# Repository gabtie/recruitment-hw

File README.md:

# Recruitment for E-Agle TRT | Electronics division

Welcome to the recruitment _test_ for the electronics team of E-Agle Trento Racing Team.

This _test_ is meant to give us the possibility to have a first understanding of the capabilities of our applicants without them having the pressure of seeing it as an exam.

Moreover it's studied so that the applicants get a first taste of the tools used, so that once in the team, they can get up and running quickly into the team's workflow without having to learn stuff under pressure when it's needed.

## What we'll look into

 - Understanding of basic electronics
 - Components choice and their suitability
 - KiCad
   - Schematic choices, tidyness and good practices
   - Board layout understanding and, again, good practices
 - `git` usage: fork, branch, clone, commit, push, pull
 - Not only _tecnical correctness_ but also actual usability.

## Assignment

Develop an overtemperature and overcurrent monitoring system (**monitor**) to perform plauysibility checks of a secondary system (**load**).

### Overview
The **monitor** has the following specs:
- It is supplied by an unstable DC voltage line, ranging from 9V to 17V
- Has a normally open relay connected in series with the load
- Has a hall effect sensor that measures the current through the load

The **load** has the following specs:
- Voltage range: $24[V] \div 48[V]$
- Current range: $-3[A] \div 25[A]$

### Specs
The **monitor** must ensure that the relay is open if the power obsorbed by the **load** is above $500[W]$.
Once open, it must not be possible to close the relay unless the **monitor** is power cycled.

No programmable logic is allowed.

The Hall effect based sensor can be chosen from the _Allegro ACS781xLR_ family of devices. Other sensors may be used as long as the specs are met and equivalency is proven.

Below you can find a general diagram of the system

## KiCad instructions
- In the schematic use also a hierarchical sheet
  - _It's not a good practice for such a small project, but it's for letting you learn about hierarchy without the hassle of a more complex assignment_

- Add comments for the necessary calculations of values

- Consider JLC PCB as the board manufacturer

## General instructions

 - Create a repository on your GitHub account (if you don't have it, create one) and copy this project in it. **Do not clone this repository!**
 - Branch the master into one called `name_surname` and commit your progress in this branch
 - Commit your progress along the way. **Do not commit just the finished project**, use Git for what it's made for!
 - When you are done, generate the schematic output inside `docs/` and the production (gerber) files in `output/`
 - If you haven't already, submit your application form [here](https://eagletrt.it/apply)
 - If you have any questions feel free to contact us at [electronics@eagletrt.it](mailto:electronics@eagletrt.it)
 - Feel free to also come to our lab (Povo 2 floor -2) if we are slow at replying
 - You have **2 weeks** (14 days) to work on this project (**This is a hard deadline and we evaluate if you meet deadlines**)

## Links
:globe_with_meridians: [Website](https://www.eagletrt.it)

:iphone: [Instagram](https://www.instagram.com/eagletrt)

:computer: [LinkedIn](https://www.linkedin.com/company/eagletrentoracingteam)

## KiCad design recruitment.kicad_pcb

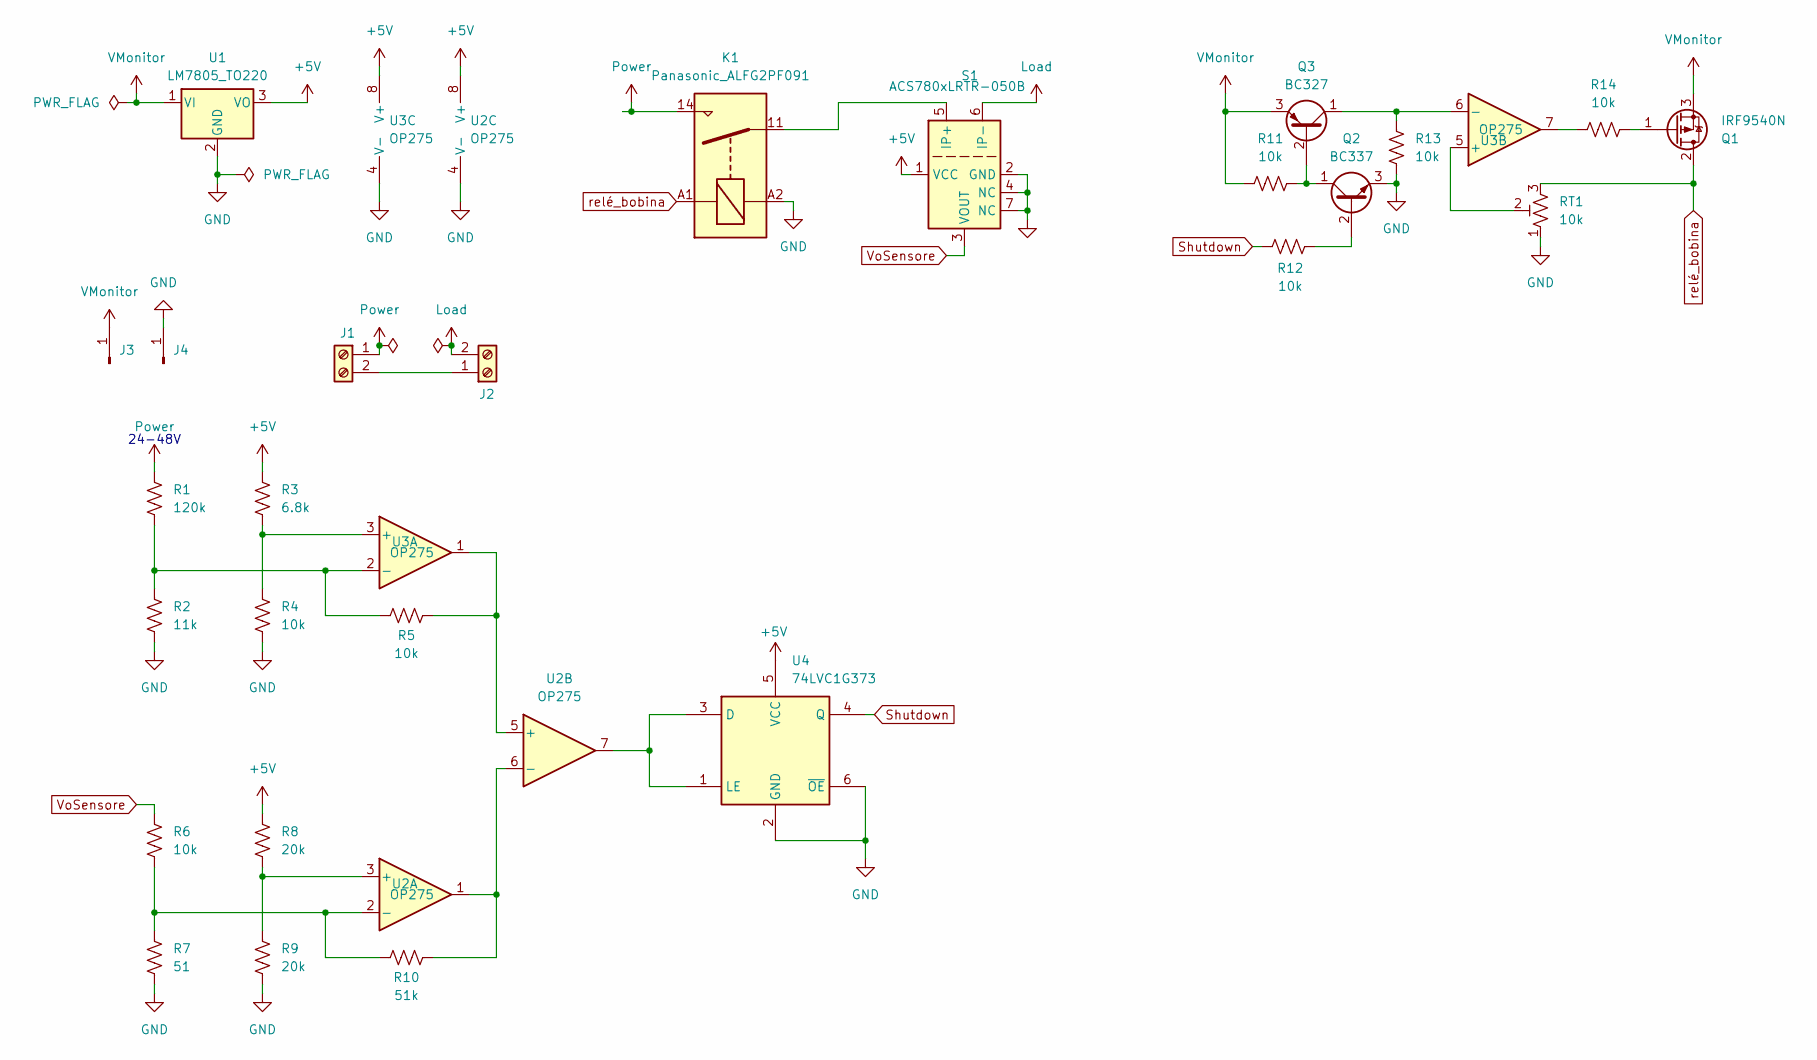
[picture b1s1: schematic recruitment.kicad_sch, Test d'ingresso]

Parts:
J1, J2: TerminalBlock_Altech_AK300-2_P5.00mm
J3, J4: Conn_01x01_Pin; PinHeader_1x01_P1.00mm_Vertical
K1: Panasonic_ALFG2PF091; Relay_SPST_Panasonic_ALFG_FormA_CircularHoles
Q1: IRF9540N; TO-220-3_Vertical
Q2: BC337; TO-92_Inline
Q3: BC327; TO-92_Inline
R1: 120k; R_1206_3216Metric
R2: 11k; R_1206_3216Metric
R3: 6.8k; R_1206_3216Metric
R4, R5, R6, R11, R12, R13, R14: 10k; R_1206_3216Metric
R7: 51; R_1206_3216Metric
R8, R9: 20k; R_1206_3216Metric
R10: 51k; R_1206_3216Metric
RT1: 10k; Potentiometer_ACP_CA6-H2,5_Horizontal
S1: ACS780xLRTR-050B; Allegro_PSOF-7_4.8x6.4mm_P1.60mm
U1: LM7805_TO220; TO-220-3_Vertical
U2, U3: OP275; SOIC-8_3.9x4.9mm_P1.27mm
U4: 74LVC1G373; SOT-23-6

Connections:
+5V: R3.2, R8.2, S1.1 (VCC), U1.3 (VO), U2.8 (V+), U3.8 (V+), U4.5 (VCC)
GND: J4.1, K1.A2, Q2.3 (E), R2.2, R4.2, R7.2, R9.2, R13.2, RT1.1, S1.2 (GND), S1.4 (NC), S1.7 (NC), U1.2 (GND), U2.4 (V-), U3.4 (V-), U4.2 (GND), U4.6 (~OE)
Load: J2.2, S1.6 (IP-)
unnamed: J1.2, J2.1
unnamed: Q1.1 (G), R14.1
unnamed: Q2.2 (B), R12.1
unnamed: Q2.1 (C), Q3.2 (B), R11.1
unnamed: Q3.1 (C), R13.1, U3.6 (-)
unnamed: R14.2, U3.7
unnamed: K1.11, S1.5 (IP+)
unnamed: R8.1, R9.1, U2.3 (+)
unnamed: R6.2, R7.1, R10.1, U2.2 (-)
unnamed: R5.2, U2.5 (+), U3.1
unnamed: R10.2, U2.1, U2.6 (-)
unnamed: R3.1, R4.1, U3.3 (+)
unnamed: R1.2, R2.1, R5.1, U3.2 (-)
unnamed: RT1.2, U3.5 (+)
unnamed: U2.7, U4.1 (LE), U4.3 (D)
Power: J1.1, K1.14, R1.1
Shutdown: R12.2, U4.4 (Q)
VMonitor: J3.1, Q1.3 (S), Q3.3 (E), R11.2, U1.1 (VI)
VoSensore: R6.1, S1.3 (VOUT)
relé_bobina: K1.A1, Q1.2 (D), RT1.3

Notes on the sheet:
24-48V

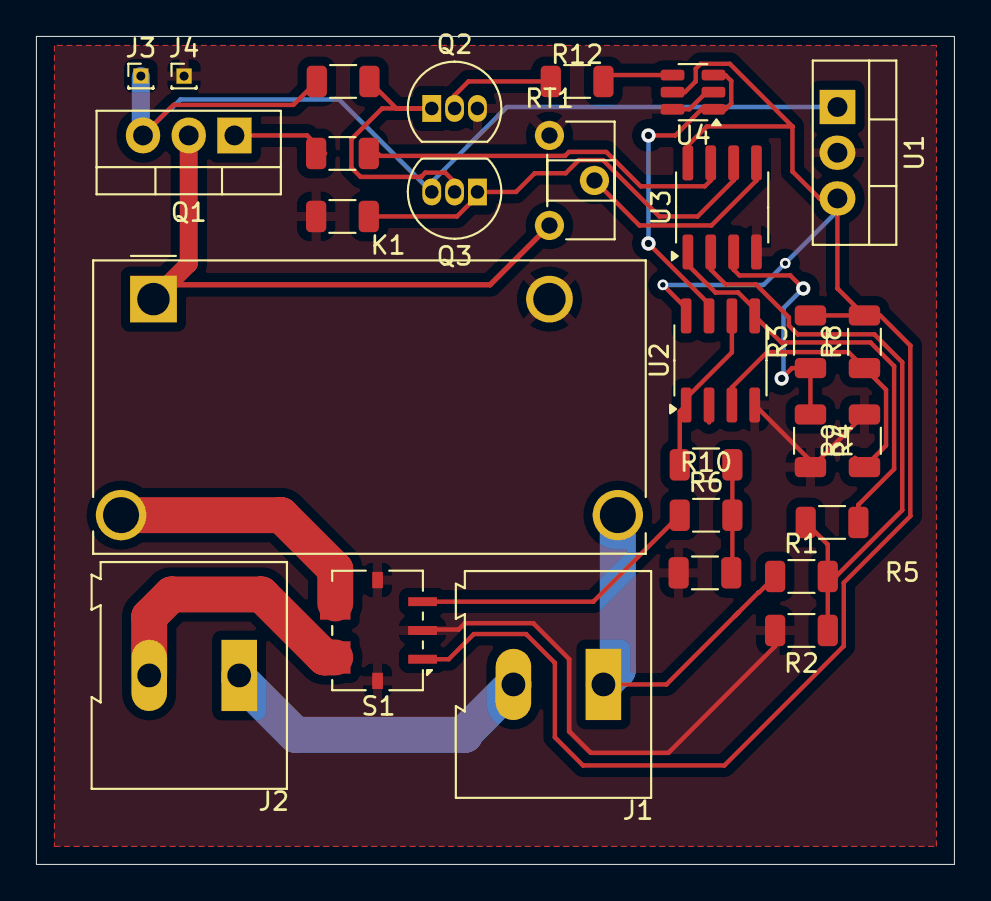
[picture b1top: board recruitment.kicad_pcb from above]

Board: 2 copper layers, 51.0 x 46.0 mm, 28 parts (0 on the bottom side), 23 nets.

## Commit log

2022-11-07 add state image
2022-12-21 update guidelines
2023-01-31 update readme with new project concept
2023-01-31 refactor: correct file name
2023-02-01 update
    added:
    - general diagram
    - components constrain
2023-02-06 small corrections
2023-03-06 remove overtemperature
2024-10-08 prova commit
2024-10-08 inizio progettazione circuito
2024-10-09 giorno 2 : prime prove e footprint
2024-10-10 prove circuiti, bisogna allineare i valori dei sensori di tensioni e corrente
2024-10-15 continuo schematica, scelta componente latch D
2024-10-16 prima prova pcb
2024-10-16 V1.0.0 : prima versione (si spera) funzionante
2024-10-16 V1.0.1 : eliminati file temporanei
2024-10-18 Aggiunto pin d'ingresso per Vmonitor, due diversi al posto di una per due perche mi dava problemi sulle distanze minime.
2025-02-25 commit 25/02/2025 risolti bug
